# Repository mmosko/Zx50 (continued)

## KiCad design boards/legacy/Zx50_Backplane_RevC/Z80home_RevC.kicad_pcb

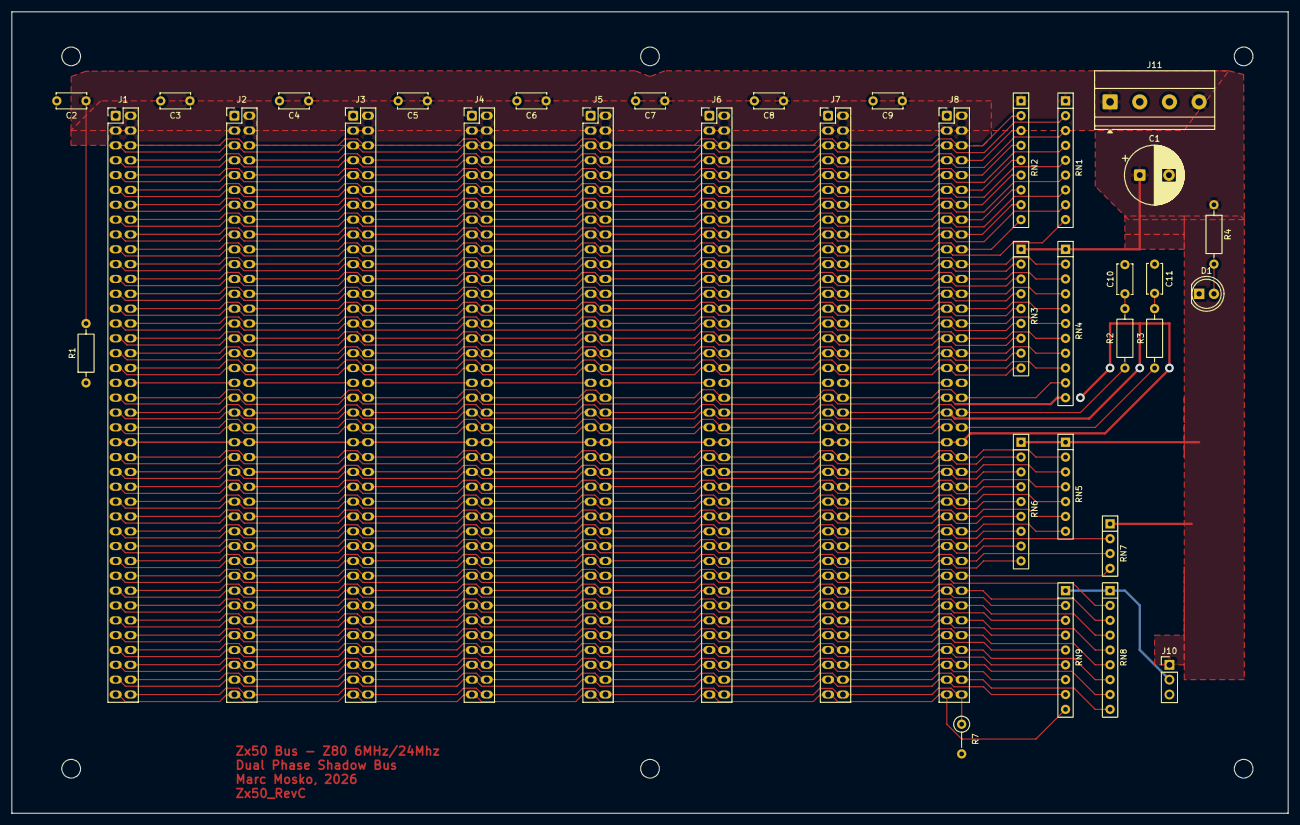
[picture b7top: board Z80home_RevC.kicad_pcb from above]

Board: 2 copper layers, 218.4 x 137.2 mm, 42 parts (0 on the bottom side), 84 nets.

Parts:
C1: 1000uf; CP_Radial_D10.0mm_P5.00mm
C2, C3, C4, C5, C6, C7, C8, C9: 0.1uF; C_Disc_D5.0mm_W2.5mm_P5.00mm
C10, C11: 100pF; C_Disc_D5.0mm_W2.5mm_P5.00mm
D1: LED; LED_D5.0mm
H1, H2, H3, H4, H5, H6: MountingHole; MountingHole_3.2mm_M3
J1, J2, J3, J4, J5, J6, J7, J8: Conn_02x40_Odd_Even; PinSocket_2x40_P2.54mm_Vertical_Oval
J10: GPIO SEL; PinHeader_1x03_P2.54mm_Vertical
J11: POWER; TerminalBlock_Phoenix_MKDS-1,5-4-5.08_1x04_P5.08mm_Horizont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
R1: 10K; R_Axial_DIN0207_L6.3mm_D2.5mm_P10.16mm_Horizontal
R2, R3: 100; R_Axial_DIN0207_L6.3mm_D2.5mm_P10.16mm_Horizontal
R4: 470; R_Axial_DIN0207_L6.3mm_D2.5mm_P10.16mm_Horizontal
R7: 10K; R_Axial_DIN0207_L6.3mm_D2.5mm_P5.08mm_Vertical
RN1, RN2, RN3, RN6, RN8, RN9: 10K; R_Array_SIP9
RN4: 4.7K; R_Array_SIP11
RN5: 2.2K; R_Array_SIP7
RN7: 10K; R_Array_SIP4

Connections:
+5V: C1.1, C2.1, C3.1, C4.1, C5.1, C6.1, C7.1, C8.1, C9.1, J1.1, J1.2, J1.3, J1.4, J2.1, J2.2, J2.3, J2.4, J3.1, J3.2, J3.3, J3.4, J4.1, J4.2, J4.3, J4.4, J5.1, J5.2, J5.3, J5.4, J6.1, J6.2, J6.3, J6.4, J7.1, J7.2, J7.3, J7.4, J8.1, J8.2, J8.3, J8.4, J10.1, J11.1, J11.4, R1.2, R4.1, R7.2, RN1.1 (common), RN2.1 (common), RN3.1 (common), RN4.1 (common), RN5.1 (common), RN6.1 (common), RN7.1 (common)
/A0: J1.5, J2.5, J3.5, J4.5, J5.5, J6.5, J7.5, J8.5, RN1.2 (R1)
/A1: J1.7, J2.7, J3.7, J4.7, J5.7, J6.7, J7.7, J8.7, RN1.3 (R2)
/A2: J1.9, J2.9, J3.9, J4.9, J5.9, J6.9, J7.9, J8.9, RN1.4 (R3)
/A3: J1.11, J2.11, J3.11, J4.11, J5.11, J6.11, J7.11, J8.11, RN1.5 (R4)
/A4: J1.13, J2.13, J3.13, J4.13, J5.13, J6.13, J7.13, J8.13, RN1.6 (R5)
/A5: J1.15, J2.15, J3.15, J4.15, J5.15, J6.15, J7.15, J8.15, RN1.7 (R6)
/A6: J1.17, J2.17, J3.17, J4.17, J5.17, J6.17, J7.17, J8.17, RN1.8 (R7)
/A7: J1.19, J2.19, J3.19, J4.19, J5.19, J6.19, J7.19, J8.19, RN1.9 (R8)
/A8: J1.21, J2.21, J3.21, J4.21, J5.21, J6.21, J7.21, J8.21, RN3.2 (R1)
/A9: J1.23, J2.23, J3.23, J4.23, J5.23, J6.23, J7.23, J8.23, RN3.3 (R2)
/A10: J1.25, J2.25, J3.25, J4.25, J5.25, J6.25, J7.25, J8.25, RN3.4 (R3)
/A11: J1.27, J2.27, J3.27, J4.27, J5.27, J6.27, J7.27, J8.27, RN3.5 (R4)
/A12: J1.29, J2.29, J3.29, J4.29, J5.29, J6.29, J7.29, J8.29, RN3.6 (R5)
/A13: J1.31, J2.31, J3.31, J4.31, J5.31, J6.31, J7.31, J8.31, RN3.7 (R6)
/A14: J1.33, J2.33, J3.33, J4.33, J5.33, J6.33, J7.33, J8.33, RN3.8 (R7)
/A15: J1.35, J2.35, J3.35, J4.35, J5.35, J6.35, J7.35, J8.35, RN3.9 (R8)
/AUX: J1.80, J2.80, J3.80, J4.80, J5.80, J6.80, J7.80, J8.80, R7.1
/CLK: J1.42, J2.42, J3.42, J4.42, J5.42, J6.42, J7.42, J8.42, R2.2
/D0: J1.6, J2.6, J3.6, J4.6, J5.6, J6.6, J7.6, J8.6, RN2.2 (R1)
/D1: J1.8, J2.8, J3.8, J4.8, J5.8, J6.8, J7.8, J8.8, RN2.3 (R2)
/D2: J1.10, J2.10, J3.10, J4.10, J5.10, J6.10, J7.10, J8.10, RN2.4 (R3)
/D3: J1.12, J2.12, J3.12, J4.12, J5.12, J6.12, J7.12, J8.12, RN2.5 (R4)
/D4: J1.14, J2.14, J3.14, J4.14, J5.14, J6.14, J7.14, J8.14, RN2.6 (R5)
/D5: J1.16, J2.16, J3.16, J4.16, J5.16, J6.16, J7.16, J8.16, RN2.7 (R6)
/D6: J1.18, J2.18, J3.18, J4.18, J5.18, J6.18, J7.18, J8.18, RN2.8 (R7)
/D7: J1.20, J2.20, J3.20, J4.20, J5.20, J6.20, J7.20, J8.20, RN2.9 (R8)
/GPIO0: J1.63, J2.63, J3.63, J4.63, J5.63, J6.63, J7.63, J8.63, RN8.2 (R1)
/GPIO1: J1.65, J2.65, J3.65, J4.65, J5.65, J6.65, J7.65, J8.65, RN9.2 (R1)
/GPIO2: J1.66, J2.66, J3.66, J4.66, J5.66, J6.66, J7.66, J8.66, RN8.3 (R2)
/GPIO3: J1.67, J2.67, J3.67, J4.67, J5.67, J6.67, J7.67, J8.67, RN9.3 (R2)
/GPIO4: J1.68, J2.68, J3.68, J4.68, J5.68, J6.68, J7.68, J8.68, RN8.4 (R3)
/GPIO5: J1.69, J2.69, J3.69, J4.69, J5.69, J6.69, J7.69, J8.69, RN9.4 (R3)
/GPIO6: J1.70, J2.70, J3.70, J4.70, J5.70, J6.70, J7.70, J8.70, RN8.5 (R4)
/GPIO7: J1.71, J2.71, J3.71, J4.71, J5.71, J6.71, J7.71, J8.71, RN9.5 (R4)
/GPIO8: J1.72, J2.72, J3.72, J4.72, J5.72, J6.72, J7.72, J8.72, RN8.6 (R5)
/GPIO9: J1.73, J2.73, J3.73, J4.73, J5.73, J6.73, J7.73, J8.73, RN9.6 (R5)
/GPIO10: J1.74, J2.74, J3.74, J4.74, J5.74, J6.74, J7.74, J8.74, RN8.7 (R6)
/GPIO11: J1.75, J2.75, J3.75, J4.75, J5.75, J6.75, J7.75, J8.75, RN9.7 (R6)
/GPIO12: J1.76, J2.76, J3.76, J4.76, J5.76, J6.76, J7.76, J8.76, RN8.8 (R7)
/GPIO13: J1.77, J2.77, J3.77, J4.77, J5.77, J6.77, J7.77, J8.77, RN9.8 (R7)
/GPIO14: J1.78, J2.78, J3.78, J4.78, J5.78, J6.78, J7.78, J8.78, RN8.9 (R8)
/GPIO15: J1.79, J2.79, J3.79, J4.79, J5.79, J6.79, J7.79, J8.79, RN9.9 (R8)
/IEI: J1.37, R1.1
/IEO: J1.38, J2.37
/IE_2_3: J2.38, J3.37
/IE_3_4: J3.38, J4.37
/IE_4_5: J4.38, J5.37
/IE_5_6: J5.38, J6.37
/IE_6_7: J6.38, J7.37
/IE_7_8: J7.38, J8.37
/MCLK: J1.44, J2.44, J3.44, J4.44, J5.44, J6.44, J7.44, J8.44, R3.1
/SD0: J1.47, J2.47, J3.47, J4.47, J5.47, J6.47, J7.47, J8.47, RN6.2 (R1)
/SD1: J1.49, J2.49, J3.49, J4.49, J5.49, J6.49, J7.49, J8.49, RN6.3 (R2)
/SD2: J1.51, J2.51, J3.51, J4.51, J5.51, J6.51, J7.51, J8.51, RN6.4 (R3)
/SD3: J1.53, J2.53, J3.53, J4.53, J5.53, J6.53, J7.53, J8.53, RN6.5 (R4)
/SD4: J1.55, J2.55, J3.55, J4.55, J5.55, J6.55, J7.55, J8.55, RN6.6 (R5)
/SD5: J1.57, J2.57, J3.57, J4.57, J5.57, J6.57, J7.57, J8.57, RN6.7 (R6)
/SD6: J1.59, J2.59, J3.59, J4.59, J5.59, J6.59, J7.59, J8.59, RN6.8 (R7)
/SD7: J1.61, J2.61, J3.61, J4.61, J5.61, J6.61, J7.61, J8.61, RN6.9 (R8)
/SRW: J1.54, J2.54, J3.54, J4.54, J5.54, J6.54, J7.54, J8.54, RN5.5 (R4)
/~BUSAK~: J1.62, J2.62, J3.62, J4.62, J5.62, J6.62, J7.62, J8.62, RN7.3 (R2)
/~BUSRQ~: J1.60, J2.60, J3.60, J4.60, J5.60, J6.60, J7.60, J8.60, RN7.2 (R1)
/~HALT~: J1.40, J2.40, J3.40, J4.40, J5.40, J6.40, J7.40, J8.40, RN4.10 (R9)
/~INT~: J1.64, J2.64, J3.64, J4.64, J5.64, J6.64, J7.64, J8.64, RN7.4 (R3)
/~IORQ~: J1.28, J2.28, J3.28, J4.28, J5.28, J6.28, J7.28, J8.28, RN4.5 (R4)
/~M1~: J1.30, J2.30, J3.30, J4.30, J5.30, J6.30, J7.30, J8.30, RN4.6 (R5)
/~MREQ~: J1.26, J2.26, J3.26, J4.26, J5.26, J6.26, J7.26, J8.26, RN4.4 (R3)
/~NMI~: J1.36, J2.36, J3.36, J4.36, J5.36, J6.36, J7.36, J8.36, RN4.9 (R8)
/~RD~: J1.22, J2.22, J3.22, J4.22, J5.22, J6.22, J7.22, J8.22, RN4.2 (R1)
/~RESET~: J1.39, J2.39, J3.39, J4.39, J5.39, J6.39, J7.39, J8.39, RN4.11 (R10)
/~RFSH~: J1.32, J2.32, J3.32, J4.32, J5.32, J6.32, J7.32, J8.32, RN4.7 (R6)
/~SINC~: J1.50, J2.50, J3.50, J4.50, J5.50, J6.50, J7.50, J8.50, RN5.3 (R2)
/~SSTB~: J1.48, J2.48, J3.48, J4.48, J5.48, J6.48, J7.48, J8.48, RN5.2 (R1)
/~S_BUSY~: J1.58, J2.58, J3.58, J4.58, J5.58, J6.58, J7.58, J8.58, RN5.7 (R6)
/~S_DONE~: J1.56, J2.56, J3.56, J4.56, J5.56, J6.56, J7.56, J8.56, RN5.6 (R5)
/~S_EN~: J1.52, J2.52, J3.52, J4.52, J5.52, J6.52, J7.52, J8.52, RN5.4 (R3)
/~WAIT~: J1.34, J2.34, J3.34, J4.34, J5.34, J6.34, J7.34, J8.34, RN4.8 (R7)
/~WR~: J1.24, J2.24, J3.24, J4.24, J5.24, J6.24, J7.24, J8.24, RN4.3 (R2)
GND: C1.2, C2.2, C3.2, C4.2, C5.2, C6.2, C7.2, C8.2, C9.2, C10.2, C11.1, D1.1 (K), J1.41, J1.43, J1.45, J1.46, J2.41, J2.43, J2.45, J2.46, J3.41, J3.43, J3.45, J3.46, J4.41, J4.43, J4.45, J4.46, J5.41, J5.43, J5.45, J5.46, J6.41, J6.43, J6.45, J6.46, J7.41, J7.43, J7.45, J7.46, J8.41, J8.43, J8.45, J8.46, J10.3, J11.2, J11.3
unnamed: C10.1, R2.1
unnamed: C11.2, R3.2
unnamed: D1.2 (A), R4.2
unnamed: J10.2, RN8.1 (common), RN9.1 (common)

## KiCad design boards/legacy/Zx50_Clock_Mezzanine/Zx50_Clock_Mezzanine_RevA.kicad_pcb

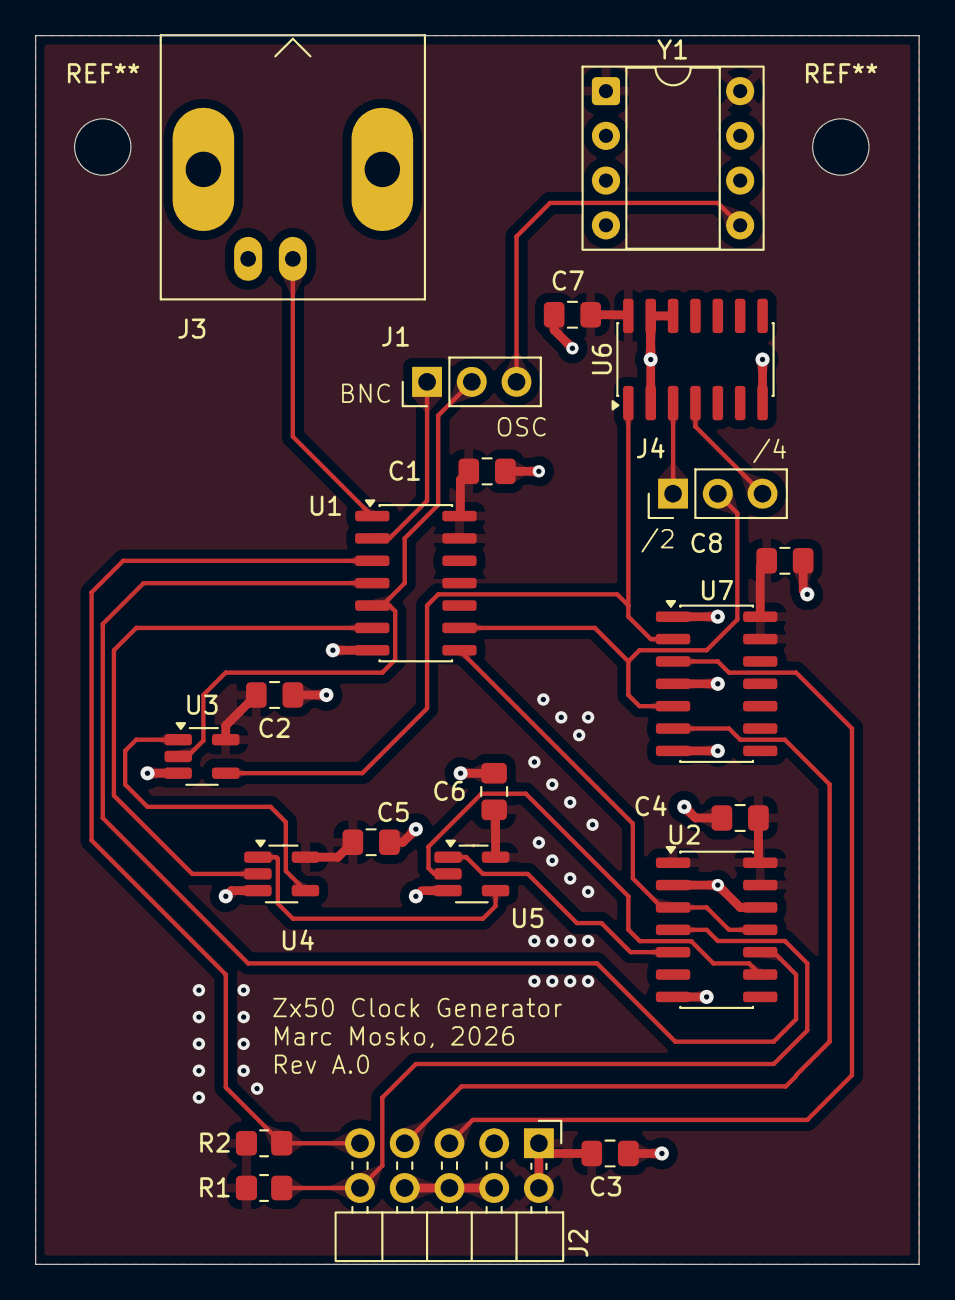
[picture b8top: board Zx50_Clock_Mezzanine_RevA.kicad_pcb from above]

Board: 2 copper layers, 50.2 x 69.8 mm, 22 parts (0 on the bottom side), 21 nets.

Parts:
C1: 0.1 uF; C_0805_2012Metric_Pad1.18x1.45mm_HandSolder
C2, C3, C4, C5, C6, C7, C8: 0.1uF; C_0805_2012Metric_Pad1.18x1.45mm_HandSolder
J1: CLK_INPUT; PinHeader_1x03_P2.54mm_Vertical
J2: Conn_02x05_Odd_Even; PinHeader_2x05_P2.54mm_Horizontal_Edge
J3: Conn_Coaxial; BNC_Amphenol_B6252HB-NPP3G-50_Horizontal
J4: CLK_DIV; PinHeader_1x03_P2.54mm_Vertical
R1, R2: 10K; R_0805_2012Metric_Pad1.20x1.40mm_HandSolder
U1: 74HC14; SOIC-14_3.9x8.7mm_P1.27mm
U2: 74HC74; SOIC-14_3.9x8.7mm_P1.27mm
U3: 74AHC1G08; SOT-23-5_HandSoldering
U4: S74LVC1G79; SOT-23-5_HandSoldering
U5: 74AHC1G32; SOT-23-5_HandSoldering
U6: 74HC393; SOIC-14_3.9x8.7mm_P1.27mm
U7: 74AHC125; SOIC-14_3.9x8.7mm_P1.27mm
Y1: SG-8002DC; DIP-8_W7.62mm_Socket

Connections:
+5V: C1.1, C2.1, C3.1, C4.1, C5.1, C6.1, C7.1, C8.1, J2.1, J2.2, R1.1, R2.1, U1.11, U1.13, U1.14 (VCC), U2.1 (1~CLR), U2.13 (2~CLR), U2.14 (VCC), U3.5 (VCC), U4.5 (VCC), U5.5 (VCC), U6.14 (VCC), U7.13 (4~OE), U7.14 (VCC), Y1.1 (OE), Y1.8 (Vcc)
/AFG_EXT_IN: J3.1 (In), U1.1
/AFG_IN: J1.1, U1.2
/ASYNC_REQ: U4.1 (D), U5.4
/DIV_2: J4.1, U6.3 (Q1A)
/DIV_4: J4.3, U6.4 (Q2A)
/MCLK_EN_SAFE: U3.1, U4.4 (Q)
/MCLK_INT: U3.4, U6.1 (CLOCKA), U7.2 (1A)
/MCLK_OUT: J2.5, U7.3 (1Y)
/MCLK_RAW: J1.2, U1.5, U3.2
/OSC_IN: J1.3, Y1.5 (OUT)
/RUN_IN: J2.9, R2.2, U1.3
/RUN_SYNC: U2.9 (2Q), U5.2
/STEP_N_IN: J2.10, R1.2, U2.4 (1~PRE)
/STEP_SYNC: U2.5 (1Q), U5.1
/ZCLK_INT: J4.2, U1.9, U7.5 (2A)
/ZCLK_OUT: J2.7, U7.6 (2Y)
/~MCLK_RAW: U1.6, U4.2 (CLK)
/~RUN_IN: U1.4, U2.10 (2~PRE)
/~ZCLK_INT: U1.8, U2.3 (1CLK), U2.11 (2CLK)
GND: C1.2, C2.2, C3.2, C4.2, C5.2, C6.2, C7.2, C8.2, J2.3, J2.4, J2.6, J2.8, J3.2 (Ext), U1.7 (GND), U2.2 (1D), U2.7 (GND), U2.12 (2D), U3.3 (GND), U4.3 (GND), U5.3 (GND), U6.2 (RESETA), U6.7 (GND), U6.12 (RESETB), U6.13 (CLOCKB), U7.1 (1~OE), U7.4 (2~OE), U7.7 (GND), U7.9 (3A), U7.10 (3~OE), U7.12 (4A), Y1.4 (GND)
